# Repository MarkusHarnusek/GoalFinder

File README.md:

# Goalfinder

## Project structure

    .
    ├── github              GitHub workflows for CI/CD
    ├── .vscode             Configuration files for Visual Studio Code
    ├── assets              Assets for development and documentation
    ├── blueprint           Hardware design files, including 3D models and PCB layouts
    ├── client              Software for the Goalfinder Board, including firmware
    ├── doc-alt             Documentation from the previous repository
    ├── web                 Development directory for the web-based access point
    ├── .gitignore          Files and directories excluded from git source control
    ├── LICENSE             Licensing information for the project
    ├── package-lock.json   Locked npm dependencies for consistent builds
    └── README.md           Description of the repository

## Credits

This project was conceived and envisioned by the [previous team](https://github.com/htl-leo-club-embedded-iot/GoalFinder)

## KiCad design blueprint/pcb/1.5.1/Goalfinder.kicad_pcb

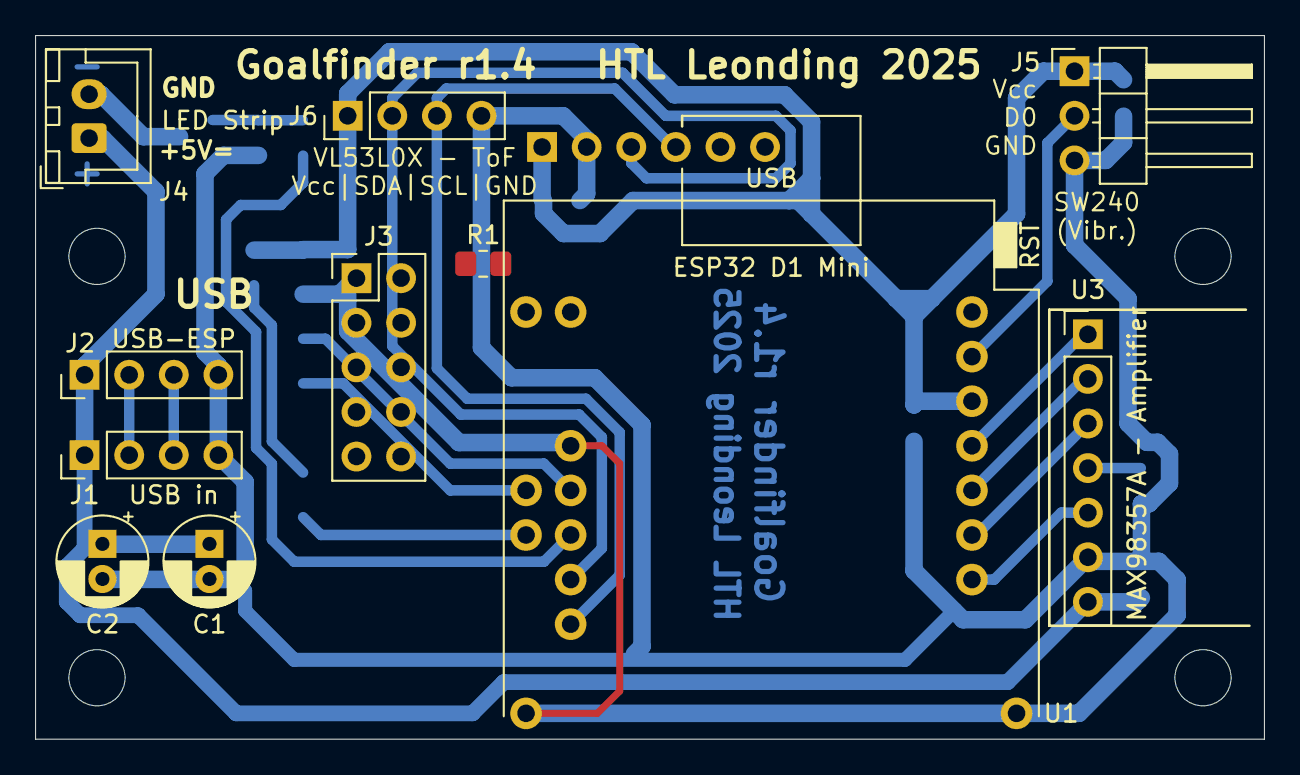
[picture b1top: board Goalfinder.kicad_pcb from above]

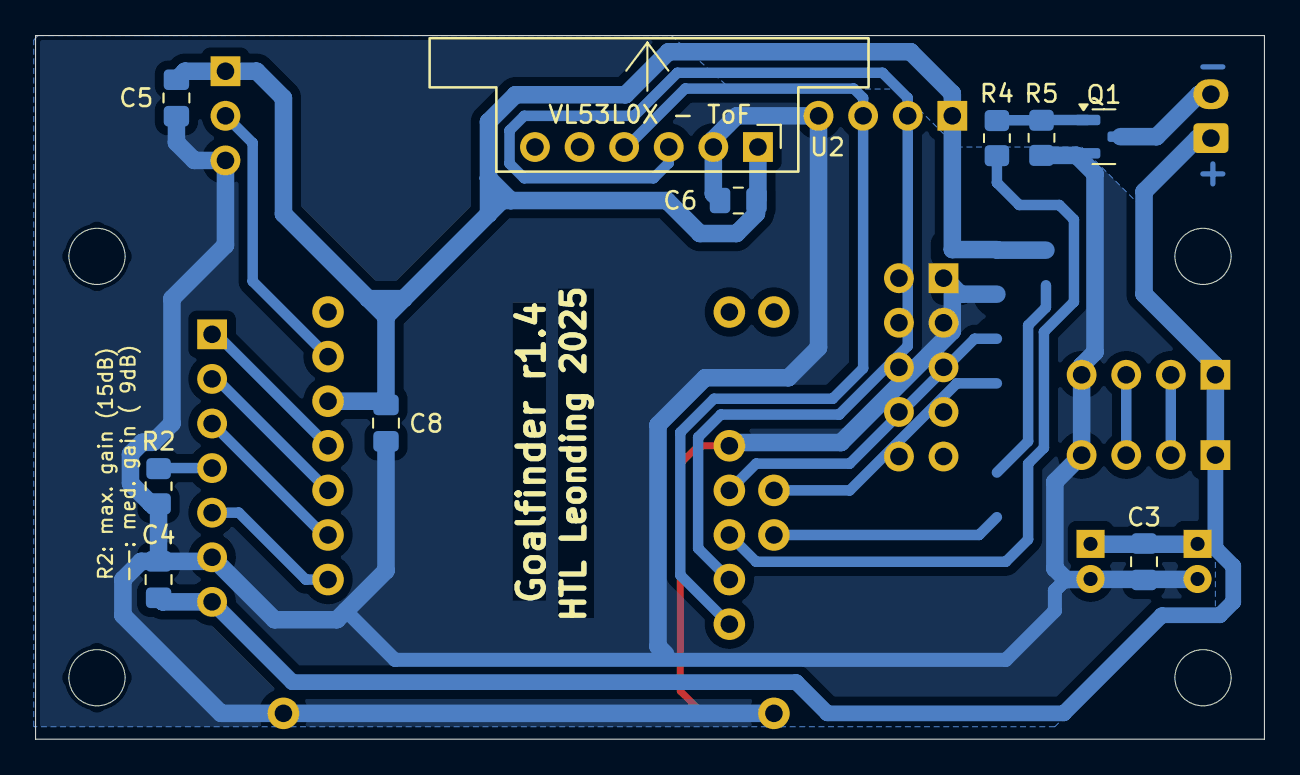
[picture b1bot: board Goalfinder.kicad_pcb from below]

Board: 2 copper layers, 70.0 x 40.1 mm, 25 parts (10 on the bottom side), 18 nets.

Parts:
C1: 22µF; CP_Radial_D5.0mm_P2.00mm
C2: 4,7µF; CP_Radial_D5.0mm_P2.00mm
C3, C4, C5, C6, C8: 100nF; C_0805_2012Metric_Pad1.18x1.45mm_HandSolder
J1: USB in; PinHeader_1x04_P2.54mm_Vertical
J2: USB-ESP; PinHeader_1x04_P2.54mm_Vertical
J3: GAIN; PinHeader_2x05_P2.54mm_Vertical
J4: LED Strip; JST_XH_B2B-XH-A_1x02_P2.50mm_Vertical
J5: SW240 - Vcc/D0/GND; PinHeader_1x03_P2.54mm_Horizontal
J6: VL53L0X-ToF Vcc/SDA/SCL/GND; PinHeader_1x04_P2.54mm_Vertical
MH1, MH2, MH3, MH4: MountingHole_3.2mm_M3
Q1: IRLML2502; SOT-23
R1, R2: 100k; R_0805_2012Metric_Pad1.20x1.40mm_HandSolder
R4: 1k; R_0805_2012Metric_Pad1.20x1.40mm_HandSolder
R5: 33k; R_0805_2012Metric_Pad1.20x1.40mm_HandSolder
U1: ESP32 D1 Mini; ESP32_D1_mini
U2: VL53L0X - ToF; VL53L0X_Breakout_Board_vertical_flat
U3: MAX98357A - Amplifier; MAX98357A_Breakout_Board

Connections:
3V3: C5.1, C6.1, C8.1, J5.1, J6.1, U1.16 (3V3), U2.1 (VCC)
5V: C1.1, C2.1, C3.1, C4.1, J1.1, J2.1, J3.3, J4.1, R1.1, U3.7 (VDD)
/LED_PWR: J4.2, Q1.3 (D)
GND: C1.2, C2.2, C3.2, C4.2, C5.2, C6.2, C8.2, J1.4, J2.4, J3.7, J5.3, J6.4, Q1.2 (S), R2.1, R5.2, U1.1 (GND), U1.22 (GND), U1.33 (GND), U2.2 (GND), U3.6 (GND)
unnamed: J1.2, J2.2
unnamed: J1.3, J2.3
unnamed: J3.1, R1.2
unnamed: J3.9, R2.2
unnamed: J5.2, U1.18 (IO_13/TCK)
unnamed: J6.2, U1.27 (IO_21/SDA_1), U2.3 (SDA)
unnamed: J6.3, U1.25 (IO_22/SCL_1), U2.4 (SCL)
unnamed: Q1.1 (G), R4.2, R5.1
unnamed: U1.14 (IO_05/SS), U3.1 (LRCLK)
unnamed: R4.1, U1.29 (IO_17/U2_TXC)
unnamed: U1.8 (IO_18/CLK), U3.5 (~SD_MODE)
unnamed: U1.10 (IO_19/MISO), U3.3 (DIN)
unnamed: U1.12 (IO_23/MOSI), U3.2 (BCLK)
unnamed: J3.2, J3.4, J3.6, J3.8, J3.10, U3.4 (GAIN_SLOT)

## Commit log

2025-10-20 added multi-threading
2025-10-20 updated settings view webapp
2025-12-17 updated git-ignores
2025-12-22 updated QR Codes and connection description
2025-12-24 Modify copyright information in LICENSE
    Updated copyright year and holder in LICENSE file.
2025-12-24 Changed .gitignore
2025-12-25 Structured housing
2025-12-25 Versioned blueprint/ subdirectories
2025-12-25 Restrucured blueprints/
2025-12-25 Sorted housing
2025-12-25 Revised PCB into new 1.5 version
2025-12-25 Copied into new 1.5.1 PCB directory
2025-12-25 Improved general and assets/ documentation
2025-12-25 Reworked Schematic to use MPU6050
2025-12-25 Cleared PCB
